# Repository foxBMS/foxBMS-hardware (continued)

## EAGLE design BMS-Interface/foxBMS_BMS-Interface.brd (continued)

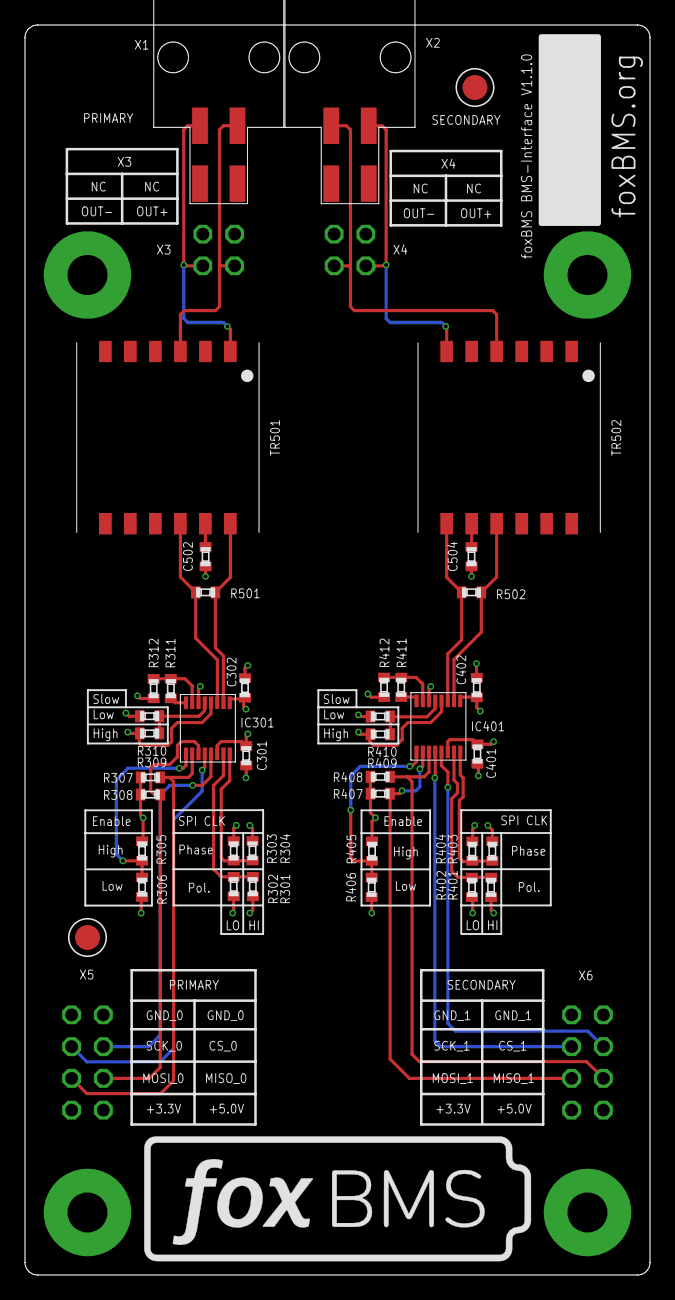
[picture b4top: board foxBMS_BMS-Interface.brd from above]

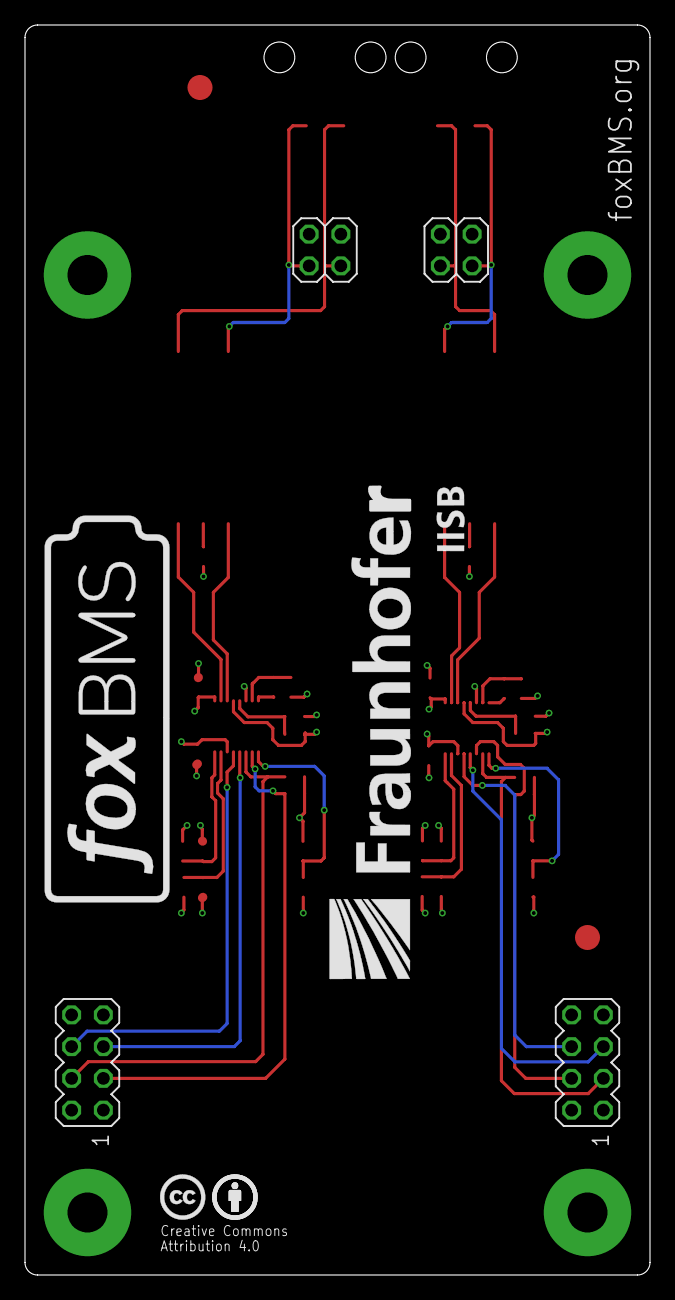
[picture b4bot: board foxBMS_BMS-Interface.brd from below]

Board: 4 copper layers, 50.0 x 100.0 mm, 44 parts (4 on the bottom side), 34 nets.

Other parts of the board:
TR501, TR502: HM2102NL
U$1, U$2: FIDUCIAL_1MM

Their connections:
unnamed 17: TR501.11; also elsewhere on the board
unnamed 23: TR502.8; also elsewhere on the board
PRIMARY_OUT+_P: TR501.3; also elsewhere on the board
PRIMARY_OUT-_N: TR501.1; also elsewhere on the board
PRIMARY_OUT_N: TR501.12; also elsewhere on the board
PRIMARY_OUT_P: TR501.10; also elsewhere on the board
SECONDARY_OUT+_P: TR502.6; also elsewhere on the board
SECONDARY_OUT-_N: TR502.4; also elsewhere on the board
SECONDARY_OUT_N: TR502.9; also elsewhere on the board
SECONDARY_OUT_P: TR502.7; also elsewhere on the board

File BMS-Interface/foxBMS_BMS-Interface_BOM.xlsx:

Populate | Qty | Value | Device | Package | Parts | Description | Farnell | Digikey | Mouser
no | 2 |  | HEADER_POS4_43045-0406 | 43045-0406 | X1, X2 | Molex - Micro-Fit 3.0 Series connector, 3.00mm (0.118) pitch header, 4 position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 | 2063766
yes | 2 |  | SSW-104-01-G-D | 2x 04 | X5, X6 | PIN HEADER | 1668340
yes | 2 |  | SSW-102-01-G-D | 2x 02 | X3, X4 | PIN HEADER | 1668329
yes | 4 | 100n | C_0603 | 603 | C301, C302, C401, C402 | Capacitor | 1828890
yes | 8 | 0R | R_0603 | 603 | R302, R304, R305, R310, R402, R404, R405, R410 | Resistor | 2059527
yes | 2 | 1.21k | R_0603 | 603 | R312, R412 | Resistor | 2059331
yes | 2 | 120 | R_0603 | 603 | R501, R502 | Resistor | 2303067
yes | 2 | 27pF | C_0603 | 603 | C502, C504 | Capacitor | 1414627
yes | 4 | 2k | R_0603 | 603 | R307, R308, R407, R408 | Resistor | 2059343
yes | 2 | 806 | R_0603 | 603 | R311, R411 | Resistor | 2059324
yes | 2 | HM2102NL | HM2102NL | HM2102NL | T501, T502
yes | 2 | LTC6820 | LTC6820 | MSOP16 | IC301, IC401 |  |  | LTC6820HMS#PBF-ND
no | 8 | OPT: 0R | R_0603 | 603 | R301, R303, R306, R309, R401, R403, R406, R409 | Resistor | 2059527

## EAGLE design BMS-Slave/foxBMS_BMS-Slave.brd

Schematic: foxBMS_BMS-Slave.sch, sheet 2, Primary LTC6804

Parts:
IC201: LTC6804HG-1#PBF; IC_SMD_SSOP-48_(G48)_R_LINEAR_REV01

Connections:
+3.0V_VREF2_0: IC201.34 (VREF2); also elsewhere on the board
+5.0V_VREG_0: IC201.37 (VREG); also elsewhere on the board
FUSED_VBAT-: IC201.30 (V-1), IC201.31 (V-2); also elsewhere on the board
PRIMARY-C0: IC201.26 (C0); also elsewhere on the board
PRIMARY-C1: IC201.24 (C1); also elsewhere on the board
PRIMARY-C2: IC201.22 (C2); also elsewhere on the board
PRIMARY-C3: IC201.20 (C3); also elsewhere on the board
PRIMARY-C4: IC201.18 (C4); also elsewhere on the board
PRIMARY-C5: IC201.16 (C5); also elsewhere on the board
PRIMARY-C6: IC201.14 (C6); also elsewhere on the board
PRIMARY-C7: IC201.12 (C7); also elsewhere on the board
PRIMARY-C8: IC201.10 (C8); also elsewhere on the board
PRIMARY-C9: IC201.8 (C9); also elsewhere on the board
PRIMARY-C10: IC201.6 (C10); also elsewhere on the board
PRIMARY-C11: IC201.4 (C11); also elsewhere on the board
PRIMARY-C12: IC201.2 (C12); also elsewhere on the board
PRIMARY-DRIVE: IC201.38 (DRIVE); also elsewhere on the board
PRIMARY-GPIO0: IC201.27 (GPIO1); also elsewhere on the board
PRIMARY-GPIO1: IC201.28 (GPIO2); also elsewhere on the board
PRIMARY-GPIO2: IC201.29 (GPIO3); also elsewhere on the board
PRIMARY-GPIO3: IC201.32 (GPIO4); also elsewhere on the board
PRIMARY-GPIO4: IC201.33 (GPIO5); also elsewhere on the board
PRIMARY-IBIAS: IC201.45 (IBIAS); also elsewhere on the board
PRIMARY-ICMP: IC201.46 (ICMP); also elsewhere on the board
PRIMARY-IN_N: IC201.41 (CSB/IMA); also elsewhere on the board
PRIMARY-IN_P: IC201.42 (SCK/IPA); also elsewhere on the board
PRIMARY-ISOMD: IC201.40 (ISOMD); also elsewhere on the board
PRIMARY-OUT_N: IC201.47 (IMB); also elsewhere on the board
PRIMARY-OUT_P: IC201.48 (IPB); also elsewhere on the board
PRIMARY-SWTEN: IC201.36 (SWTEN); also elsewhere on the board
PRIMARY-V+: IC201.1 (V+); also elsewhere on the board
PRIMARY-VREF1: IC201.35 (VREF1); also elsewhere on the board
PRIMARY-WDT: IC201.39 (WDT); also elsewhere on the board
S0: IC201.25 (S1); also elsewhere on the board
S1: IC201.23 (S2); also elsewhere on the board
S2: IC201.21 (S3); also elsewhere on the board
S3: IC201.19 (S4); also elsewhere on the board
S4: IC201.17 (S5); also elsewhere on the board
S5: IC201.15 (S6); also elsewhere on the board
S6: IC201.13 (S7); also elsewhere on the board
S7: IC201.11 (S8); also elsewhere on the board
S8: IC201.9 (S9); also elsewhere on the board
S9: IC201.7 (S10); also elsewhere on the board
S10: IC201.5 (S11); also elsewhere on the board
S11: IC201.3 (S12); also elsewhere on the board

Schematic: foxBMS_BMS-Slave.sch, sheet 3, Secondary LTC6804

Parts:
IC301: LTC6804HG-1#PBF; IC_SMD_SSOP-48_(G48)_R_LINEAR_REV01

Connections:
+3.0V_VREF2_1: IC301.34 (VREF2); also elsewhere on the board
+5.0V_VREG_1: IC301.37 (VREG); also elsewhere on the board
FUSED_VBAT-: IC301.30 (V-1), IC301.31 (V-2); also elsewhere on the board
SECONDARY-C0: IC301.26 (C0); also elsewhere on the board
SECONDARY-C1: IC301.24 (C1); also elsewhere on the board
SECONDARY-C2: IC301.22 (C2); also elsewhere on the board
SECONDARY-C3: IC301.20 (C3); also elsewhere on the board
SECONDARY-C4: IC301.18 (C4); also elsewhere on the board
SECONDARY-C5: IC301.16 (C5); also elsewhere on the board
SECONDARY-C6: IC301.14 (C6); also elsewhere on the board
SECONDARY-C7: IC301.12 (C7); also elsewhere on the board
SECONDARY-C8: IC301.10 (C8); also elsewhere on the board
SECONDARY-C9: IC301.8 (C9); also elsewhere on the board
SECONDARY-C10: IC301.6 (C10); also elsewhere on the board
SECONDARY-C11: IC301.4 (C11); also elsewhere on the board
SECONDARY-C12: IC301.2 (C12); also elsewhere on the board
SECONDARY-DRIVE: IC301.38 (DRIVE); also elsewhere on the board
SECONDARY-GPIO0: IC301.27 (GPIO1); also elsewhere on the board
SECONDARY-GPIO1: IC301.28 (GPIO2); also elsewhere on the board
SECONDARY-GPIO2: IC301.29 (GPIO3); also elsewhere on the board
SECONDARY-GPIO3: IC301.32 (GPIO4); also elsewhere on the board
SECONDARY-GPIO4: IC301.33 (GPIO5); also elsewhere on the board
SECONDARY-IBIAS: IC301.45 (IBIAS); also elsewhere on the board
SECONDARY-ICMP: IC301.46 (ICMP); also elsewhere on the board
SECONDARY-IN_N: IC301.41 (CSB/IMA); also elsewhere on the board
SECONDARY-IN_P: IC301.42 (SCK/IPA); also elsewhere on the board
SECONDARY-ISOMD: IC301.40 (ISOMD); also elsewhere on the board
SECONDARY-OUT_N: IC301.47 (IMB); also elsewhere on the board
SECONDARY-OUT_P: IC301.48 (IPB); also elsewhere on the board
SECONDARY-SWTEN: IC301.36 (SWTEN); also elsewhere on the board
SECONDARY-V+: IC301.1 (V+); also elsewhere on the board
SECONDARY-VREF1: IC301.35 (VREF1); also elsewhere on the board
SECONDARY-WDT: IC301.39 (WDT); also elsewhere on the board

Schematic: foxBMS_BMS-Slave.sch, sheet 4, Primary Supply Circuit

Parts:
C401, C403, C405: 1uF, 20%, 16V; 0603
C402, C404, C406: 100nF, 10%, 100V; 0805
LSP401, LSP402, LSP403: PAD_2.0X1.5MM; PAD2.0X1.5MM
R401, R402: 100R, 1%, 1/10W; 0603
T401: PBHV8115Z; D_SMD_SOT223_(SC-73)_R_NXP_REV01
Z401: 60V,500mW; D_SMD_SOD-123_R_ON_REV01

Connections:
+3.0V_VREF2_0: C401.2, LSP403.P$1; also elsewhere on the board
+5.0V_VREG_0: C405.2, LSP401.P$1, T401.3 (E); also elsewhere on the board
FUSED_VBAT+: R401.2, R402.1; also elsewhere on the board
FUSED_VBAT-: C401.1, C402.2, C403.1, C404.2, C405.1, C406.1, Z401.A; also elsewhere on the board
unnamed: C406.2, R401.1, T401.2 (C), T401.4 (C)
PRIMARY-DRIVE: T401.1 (B); also elsewhere on the board
PRIMARY-V+: C402.1, C404.1, R402.2, Z401.K (C); also elsewhere on the board
PRIMARY-VREF1: C403.2, LSP402.P$1; also elsewhere on the board

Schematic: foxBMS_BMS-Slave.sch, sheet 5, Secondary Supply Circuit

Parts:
C501, C503, C505: 1uF, 20%, 16V; 0603
C502, C504, C506: 100nF, 10%, 100V; 0805
LSP501, LSP502, LSP503: PAD_2.0X1.5MM; PAD2.0X1.5MM
R501, R502: 100R, 1%, 1/10W; 0603
T501: PBHV8115Z; D_SMD_SOT223_(SC-73)_R_NXP_REV01
Z501: 60V,500mW; D_SMD_SOD-123_R_ON_REV01

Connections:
+3.0V_VREF2_1: C501.2, LSP503.P$1; also elsewhere on the board
+5.0V_VREG_1: C505.2, LSP501.P$1, T501.3 (E); also elsewhere on the board
FUSED_VBAT+: R501.2, R502.1; also elsewhere on the board
FUSED_VBAT-: C501.1, C502.2, C503.1, C504.2, C505.1, C506.1, Z501.A; also elsewhere on the board
unnamed: C506.2, R501.1, T501.2 (C), T501.4 (C)
SECONDARY-DRIVE: T501.1 (B); also elsewhere on the board
SECONDARY-V+: C502.1, C504.1, R502.2, Z501.K (C); also elsewhere on the board
SECONDARY-VREF1: C503.2, LSP502.P$1; also elsewhere on the board

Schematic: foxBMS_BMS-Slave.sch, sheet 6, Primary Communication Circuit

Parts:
C601, C602: 100pF, 15%, 25V; 0603
C603, C604: 1uF, 20%, 25V; 0603
LSP601, LSP602, LSP603, LSP604: PAD_2.0X1.5MM; PAD2.0X1.5MM
R601, R607: 0R; 0603
R602: 806, 1%, 1/10W; 0603
R603: 1.21k, 1%, 1/10W; 0603
R604, R605: 120R, 1%, 1/10W; 0603
R606: OPT: 0R; 0603
R608: 1M, 10%, 1/10W; 0603
TR601: HX1188NL; TR_SMD_SOIC-16_(12,70MMX9,53MMX5,97MM)_R_PULSE_REV01

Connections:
+5.0V_VREG_0: R601.2, R606.2, R608.2; also elsewhere on the board
FUSED_VBAT-: C601.1, C602.1, R603.2, R607.1; also elsewhere on the board
GND_1: C603.1, C604.1; also elsewhere on the board
unnamed: C601.2, TR601.2 (CT)
unnamed: C602.2, TR601.7 (CT)
unnamed: C604.2, TR601.15 (CMT)
unnamed: C603.2, TR601.10 (CMT)
PRIMARY-IBIAS: R602.1; also elsewhere on the board
PRIMARY-ICMP: R602.2, R603.1; also elsewhere on the board
PRIMARY-IN+_P: LSP601.P$1, TR601.16 (X+); also elsewhere on the board
PRIMARY-IN-_N: LSP602.P$1, TR601.14 (X-); also elsewhere on the board
PRIMARY-IN_N: R604.2, TR601.3 (D-); also elsewhere on the board
PRIMARY-IN_P: R604.1, TR601.1 (D+); also elsewhere on the board
PRIMARY-ISOMD: R601.1; also elsewhere on the board
PRIMARY-OUT+_P: LSP603.P$1, TR601.11 (X+); also elsewhere on the board
PRIMARY-OUT-_N: LSP604.P$1, TR601.9 (X-); also elsewhere on the board
PRIMARY-OUT_N: R605.2, TR601.8 (D-); also elsewhere on the board
PRIMARY-OUT_P: R605.1, TR601.6 (D+); also elsewhere on the board
PRIMARY-SWTEN: R606.1, R607.2; also elsewhere on the board
PRIMARY-WDT: R608.1; also elsewhere on the board

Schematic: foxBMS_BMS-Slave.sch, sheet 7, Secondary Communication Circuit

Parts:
C701, C702: 100pF, 15%, 25V; 0603
C703, C704: 1uF, 20%, 25V; 0603
LSP701, LSP702, LSP703, LSP704: PAD_2.0X1.5MM; PAD2.0X1.5MM
R701, R707: 0R; 0603
R702: 806, 1%, 1/10W; 0603
R703: 1.21k, 1%, 1/10W; 0603
R704, R705: 120R, 1%, 1/10W; 0603
R706: OPT: 0R; 0603
R708: 1M, 10%, 1/10W; 0603
TR701: HX1188NL; TR_SMD_SOIC-16_(12,70MMX9,53MMX5,97MM)_R_PULSE_REV01

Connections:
+5.0V_VREG_1: R701.2, R706.2, R708.2; also elsewhere on the board
FUSED_VBAT-: C701.1, C702.1, R703.2, R707.1; also elsewhere on the board
GND_1: C703.1, C704.1; also elsewhere on the board
unnamed: C701.2, TR701.2 (CT)
unnamed: C702.2, TR701.7 (CT)
unnamed: C704.2, TR701.15 (CMT)
unnamed: C703.2, TR701.10 (CMT)
SECONDARY-IBIAS: R702.1; also elsewhere on the board
SECONDARY-ICMP: R702.2, R703.1; also elsewhere on the board
SECONDARY-IN+_P: LSP701.P$1, TR701.16 (X+); also elsewhere on the board
SECONDARY-IN-_N: LSP702.P$1, TR701.14 (X-); also elsewhere on the board
SECONDARY-IN_N: R704.2, TR701.3 (D-); also elsewhere on the board
SECONDARY-IN_P: R704.1, TR701.1 (D+); also elsewhere on the board
SECONDARY-ISOMD: R701.1; also elsewhere on the board
SECONDARY-OUT+_P: LSP703.P$1, TR701.11 (X+); also elsewhere on the board
SECONDARY-OUT-_N: LSP704.P$1, TR701.9 (X-); also elsewhere on the board
SECONDARY-OUT_N: R705.2, TR701.8 (D-); also elsewhere on the board
SECONDARY-OUT_P: R705.1, TR701.6 (D+); also elsewhere on the board
SECONDARY-SWTEN: R706.1, R707.2; also elsewhere on the board
SECONDARY-WDT: R708.1; also elsewhere on the board

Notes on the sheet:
standard = off

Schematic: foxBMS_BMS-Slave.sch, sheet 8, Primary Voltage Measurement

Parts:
C801, C802, C803, C804, C805, C806, C807, C815, C816, C817, C818, C819, C820: 10nF, 100V, 10%; 0603
C808, C809, C810, C811, C812, C813, C814, C821, C822, C823, C824, C825, C826: OPT: 100nF, 25V; 0805
R801, R802, R803, R804, R805, R806, R807, R808, R809, R810, R811, R812, R813: 100R, 1%, 1/10W; 0603
Z801, Z802, Z803, Z804, Z805, Z806, Z807, Z808, Z809, Z810, Z811, Z812, Z813: 6.8V, 500mW; D_SMD_SOD-123_R_ON_REV01

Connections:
FUSED_CELL_0+: R806.1; also elsewhere on the board
FUSED_CELL_0-: R807.1; also elsewhere on the board
FUSED_CELL_1+: R805.1; also elsewhere on the board
FUSED_CELL_2+: R804.1; also elsewhere on the board
FUSED_CELL_3+: R803.1; also elsewhere on the board
FUSED_CELL_4+: R802.1; also elsewhere on the board
FUSED_CELL_5+: R801.1; also elsewhere on the board
FUSED_CELL_6+: R813.1; also elsewhere on the board
FUSED_CELL_7+: R812.1; also elsewhere on the board
FUSED_CELL_8+: R811.1; also elsewhere on the board
FUSED_CELL_9+: R810.1; also elsewhere on the board
FUSED_CELL_10+: R809.1; also elsewhere on the board
FUSED_CELL_11+: R808.1; also elsewhere on the board
FUSED_VBAT-: C801.2, C802.2, C803.2, C804.2, C805.2, C806.2, C807.2, C814.1, C815.2, C816.2, C817.2, C818.2, C819.2, C820.2, Z807.A; also elsewhere on the board
PRIMARY-C0: C807.1, C813.1, C814.2, R807.2, Z806.A, Z807.K (C); also elsewhere on the board
PRIMARY-C1: C806.1, C812.1, C813.2, R806.2, Z805.A, Z806.K (C); also elsewhere on the board
PRIMARY-C2: C805.1, C811.1, C812.2, R805.2, Z804.A, Z805.K (C); also elsewhere on the board
PRIMARY-C3: C804.1, C810.1, C811.2, R804.2, Z803.A, Z804.K (C); also elsewhere on the board
PRIMARY-C4: C803.1, C809.1, C810.2, R803.2, Z802.A, Z803.K (C); also elsewhere on the board
PRIMARY-C5: C802.1, C808.1, C809.2, R802.2, Z801.A, Z802.K (C); also elsewhere on the board
PRIMARY-C6: C801.1, C808.2, C826.1, R801.2, Z801.K (C), Z813.A; also elsewhere on the board
PRIMARY-C7: C820.1, C825.1, C826.2, R813.2, Z812.A, Z813.K (C); also elsewhere on the board
PRIMARY-C8: C819.1, C824.1, C825.2, R812.2, Z811.A, Z812.K (C); also elsewhere on the board
PRIMARY-C9: C818.1, C823.1, C824.2, R811.2, Z810.A, Z811.K (C); also elsewhere on the board
PRIMARY-C10: C817.1, C822.1, C823.2, R810.2, Z809.A, Z810.K (C); also elsewhere on the board
PRIMARY-C11: C816.1, C821.1, C822.2, R809.2, Z808.A, Z809.K (C); also elsewhere on the board
PRIMARY-C12: C815.1, C821.2, R808.2, Z808.K (C); also elsewhere on the board

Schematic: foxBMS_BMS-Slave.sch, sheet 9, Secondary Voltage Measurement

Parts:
C901, C902, C903, C904, C905, C906, C907, C915, C916, C917, C918, C919, C920: 10nF, 100V, 10%; 0603
C908, C909, C910, C911, C912, C913, C914, C921, C922, C923, C924, C925, C926: OPT: 100nF, 25V; 0805
R901, R902, R903, R904, R905, R906, R907, R908, R909, R910, R911, R912, R913: 100R, 1%, 1/10W; 0603
Z901, Z902, Z903, Z904, Z905, Z906, Z907, Z908, Z909, Z910, Z911, Z912, Z913: 6.8V, 500mW; D_SMD_SOD-123_R_ON_REV01

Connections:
FUSED_CELL_0+: R906.1; also elsewhere on the board
FUSED_CELL_0-: R907.1; also elsewhere on the board
FUSED_CELL_1+: R905.1; also elsewhere on the board
FUSED_CELL_2+: R904.1; also elsewhere on the board
FUSED_CELL_3+: R903.1; also elsewhere on the board
FUSED_CELL_4+: R902.1; also elsewhere on the board
FUSED_CELL_5+: R901.1; also elsewhere on the board
FUSED_CELL_6+: R913.1; also elsewhere on the board
FUSED_CELL_7+: R912.1; also elsewhere on the board
FUSED_CELL_8+: R911.1; also elsewhere on the board
FUSED_CELL_9+: R910.1; also elsewhere on the board
FUSED_CELL_10+: R909.1; also elsewhere on the board
FUSED_CELL_11+: R908.1; also elsewhere on the board
FUSED_VBAT-: C901.2, C902.2, C903.2, C904.2, C905.2, C906.2, C907.2, C914.1, C915.2, C916.2, C917.2, C918.2, C919.2, C920.2, Z907.A; also elsewhere on the board
SECONDARY-C0: C907.1, C913.1, C914.2, R907.2, Z906.A, Z907.K (C); also elsewhere on the board
SECONDARY-C1: C906.1, C912.1, C913.2, R906.2, Z905.A, Z906.K (C); also elsewhere on the board
SECONDARY-C2: C905.1, C911.1, C912.2, R905.2, Z904.A, Z905.K (C); also elsewhere on the board
SECONDARY-C3: C904.1, C910.1, C911.2, R904.2, Z903.A, Z904.K (C); also elsewhere on the board
SECONDARY-C4: C903.1, C909.1, C910.2, R903.2, Z902.A, Z903.K (C); also elsewhere on the board
SECONDARY-C5: C902.1, C908.1, C909.2, R902.2, Z901.A, Z902.K (C); also elsewhere on the board
SECONDARY-C6: C901.1, C908.2, C926.1, R901.2, Z901.K (C), Z913.A; also elsewhere on the board
SECONDARY-C7: C920.1, C925.1, C926.2, R913.2, Z912.A, Z913.K (C); also elsewhere on the board
SECONDARY-C8: C919.1, C924.1, C925.2, R912.2, Z911.A, Z912.K (C); also elsewhere on the board
SECONDARY-C9: C918.1, C923.1, C924.2, R911.2, Z910.A, Z911.K (C); also elsewhere on the board
SECONDARY-C10: C917.1, C922.1, C923.2, R910.2, Z909.A, Z910.K (C); also elsewhere on the board
SECONDARY-C11: C916.1, C921.1, C922.2, R909.2, Z908.A, Z909.K (C); also elsewhere on the board
SECONDARY-C12: C915.1, C921.2, R908.2, Z908.K (C); also elsewhere on the board

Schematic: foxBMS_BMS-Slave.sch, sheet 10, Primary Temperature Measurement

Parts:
C1001: 100nF, 20%, 16V; 0603
C1002, C1003, C1004: 1uF, 20%, 16V; 0603
C1005: 10nF, 20%, 16V; 0603
M1001, M1002: LTC1380CGN; IC_SMD_SSOP-16_(GN16)_R_LINEAR_REV01
O1001: LTC6255CS6; IC_SMD_TSOT-23-6_(S6)_R_LINEAR_REV01
R1001, R1002, R1003, R1004, R1005, R1006, R1007, R1008, R1009, R1010, R1011, R1012, R1013, R1014, R1015, R1016: 20k, 1%, 1/10W; 0603
R1017, R1018: 4.7k, 10%, 1/10W; 0603
R1019, R1021, R1023: N/A; 0603
R1020, R1022, R1024: 0R; 0603
R1025: 100R, 1%, 1/10W; 0603
SJ1001: OPT; SJ

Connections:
+3.0V_VREF2_0: C1001.2, R1001.2, R1002.2, R1003.2, R1004.2, R1005.2, R1006.2, R1007.2, R1008.2, R1009.2, R1010.2, R1011.2, R1012.2, R1013.2, R1014.2, R1015.2, R1016.2; also elsewhere on the board
+5.0V_VREG_0: C1002.2, C1003.2, C1004.2, M1001.16 (VCC), M1002.13 (A0), M1002.16 (VCC), O1001.6 (V+), R1017.2, R1018.2; also elsewhere on the board
FUSED_VBAT-: C1001.1, C1002.1, C1003.1, C1004.1, C1005.1, M1001.10 (VEE), M1001.11 (GND), M1001.12 (A1), M1001.13 (A0), M1002.10 (VEE), M1002.11 (GND), M1002.12 (A1), O1001.2 (V-); also elsewhere on the board
unnamed: O1001.1 (VOUT), O1001.4 (-), R1025.1
unnamed: O1001.5 (!SHDN), SJ1001.1
PRIMARY-GPIO0: R1023.2, R1024.2; also elsewhere on the board
PRIMARY-GPIO0-OPT: R1023.1; also elsewhere on the board
PRIMARY-GPIO2: SJ1001.2; also elsewhere on the board
PRIMARY-GPIO3: R1021.2, R1022.2; also elsewhere on the board
PRIMARY-GPIO3-OPT: R1021.1; also elsewhere on the board
PRIMARY-GPIO4: R1019.2, R1020.2; also elsewhere on the board
PRIMARY-GPIO4-OPT: R1019.1; also elsewhere on the board
PRIMARY-MUX-DATA: C1005.2, R1024.1, R1025.2
PRIMARY-OPA_IN: M1001.9 (DO), M1002.9 (DO), O1001.3 (+); also elsewhere on the board
PRIMARY-SCL: M1001.15 (SCL), M1002.15 (SCL), R1017.1, R1020.1; also elsewhere on the board
PRIMARY-SDA: M1001.14 (SDA), M1002.14 (SDA), R1018.1, R1022.1; also elsewhere on the board
T-SENSOR_0: M1001.1 (S0), R1015.1; also elsewhere on the board
T-SENSOR_1: M1001.2 (S1), R1013.1; also elsewhere on the board
T-SENSOR_2: M1001.3 (S2), R1011.1; also elsewhere on the board
T-SENSOR_3: M1001.4 (S3), R1009.1; also elsewhere on the board
T-SENSOR_4: M1001.5 (S4), R1007.1; also elsewhere on the board
T-SENSOR_5: M1001.6 (S5), R1005.1; also elsewhere on the board
T-SENSOR_6: M1001.7 (S6), R1003.1; also elsewhere on the board
T-SENSOR_7: M1001.8 (S7), R1001.1; also elsewhere on the board
T-SENSOR_8: M1002.1 (S0), R1016.1; also elsewhere on the board
T-SENSOR_9: M1002.2 (S1), R1014.1; also elsewhere on the board
T-SENSOR_10: M1002.3 (S2), R1012.1; also elsewhere on the board
T-SENSOR_11: M1002.4 (S3), R1010.1; also elsewhere on the board
T-SENSOR_12: M1002.5 (S4), R1008.1; also elsewhere on the board
T-SENSOR_13: M1002.6 (S5), R1006.1; also elsewhere on the board
T-SENSOR_14: M1002.7 (S6), R1004.1; also elsewhere on the board
T-SENSOR_15: M1002.8 (S7), R1002.1; also elsewhere on the board

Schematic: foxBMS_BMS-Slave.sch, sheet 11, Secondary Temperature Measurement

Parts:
C1101: 100nF, 20%, 16V; 0603
C1102, C1103, C1104: 1uF, 20%, 16V; 0603
C1105: 10nF, 20%, 16V; 0603
M1101, M1102: LTC1380CGN; IC_SMD_SSOP-16_(GN16)_R_LINEAR_REV01
O1101: LTC6255CS6; IC_SMD_TSOT-23-6_(S6)_R_LINEAR_REV01
R1101, R1102, R1103, R1104, R1105, R1106, R1107, R1108, R1109, R1110, R1111, R1112, R1113, R1114, R1115, R1116: 20k, 1%, 1/10W; 0603
R1117, R1118: 4.7k, 10%, 1/10W; 0603
R1119, R1121, R1123: OPT: 0R; 0603
R1120, R1122, R1124: 0R; 0603
R1125: 100R, 1%, 1/10W; 0603
SJ1101: OPT; SJ

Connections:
+3.0V_VREF2_1: C1101.2, R1101.2, R1102.2, R1103.2, R1104.2, R1105.2, R1106.2, R1107.2, R1108.2, R1109.2, R1110.2, R1111.2, R1112.2, R1113.2, R1114.2, R1115.2, R1116.2; also elsewhere on the board
+5.0V_VREG_1: C1102.2, C1103.2, C1104.2, M1101.16 (VCC), M1102.13 (A0), M1102.16 (VCC), O1101.6 (V+), R1117.2, R1118.2; also elsewhere on the board
FUSED_VBAT-: C1101.1, C1102.1, C1103.1, C1104.1, C1105.1, M1101.10 (VEE), M1101.11 (GND), M1101.12 (A1), M1101.13 (A0), M1102.10 (VEE), M1102.11 (GND), M1102.12 (A1), O1101.2 (V-); also elsewhere on the board
unnamed: O1101.5 (!SHDN), SJ1101.1
unnamed: O1101.1 (VOUT), O1101.4 (-), R1125.1
SECONDARY-GPIO0: R1123.2, R1124.2; also elsewhere on the board
SECONDARY-GPIO0-OPT: R1123.1; also elsewhere on the board
SECONDARY-GPIO2: SJ1101.2; also elsewhere on the board
SECONDARY-GPIO3: R1121.2, R1122.2; also elsewhere on the board
SECONDARY-GPIO3-OPT: R1121.1; also elsewhere on the board
SECONDARY-GPIO4: R1119.2, R1120.2; also elsewhere on the board
SECONDARY-GPIO4-OPT: R1119.1; also elsewhere on the board
SECONDARY-MUX-DATA: C1105.2, R1124.1, R1125.2
SECONDARY-OPA_IN: M1101.9 (DO), M1102.9 (DO), O1101.3 (+); also elsewhere on the board
SECONDARY-SCL: M1101.15 (SCL), M1102.15 (SCL), R1117.1, R1120.1; also elsewhere on the board
SECONDARY-SDA: M1101.14 (SDA), M1102.14 (SDA), R1118.1, R1122.1; also elsewhere on the board
T-SENSOR_16: M1101.1 (S0), R1115.1; also elsewhere on the board
T-SENSOR_17: M1101.2 (S1), R1113.1; also elsewhere on the board
T-SENSOR_18: M1101.3 (S2), R1111.1; also elsewhere on the board
T-SENSOR_19: M1101.4 (S3), R1109.1; also elsewhere on the board
T-SENSOR_20: M1101.5 (S4), R1107.1; also elsewhere on the board
T-SENSOR_21: M1101.6 (S5), R1105.1; also elsewhere on the board
T-SENSOR_22: M1101.7 (S6), R1103.1; also elsewhere on the board
T-SENSOR_23: M1101.8 (S7), R1101.1; also elsewhere on the board
T-SENSOR_24: M1102.1 (S0), R1116.1; also elsewhere on the board
T-SENSOR_25: M1102.2 (S1), R1114.1; also elsewhere on the board
T-SENSOR_26: M1102.3 (S2), R1112.1; also elsewhere on the board
T-SENSOR_27: M1102.4 (S3), R1110.1; also elsewhere on the board
T-SENSOR_28: M1102.5 (S4), R1108.1; also elsewhere on the board
T-SENSOR_29: M1102.6 (S5), R1106.1; also elsewhere on the board
T-SENSOR_30: M1102.7 (S6), R1104.1; also elsewhere on the board
T-SENSOR_31: M1102.8 (S7), R1102.1; also elsewhere on the board

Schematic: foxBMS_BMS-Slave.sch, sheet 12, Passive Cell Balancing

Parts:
R1201, R1202, R1203, R1204, R1205, R1206, R1207, R1208, R1209, R1210, R1211, R1212, R1219, R1220, R1221, R1222, R1223, R1224, R1225, R1226, R1227, R1228, R1229, R1230: 75R, 10%, 0.4W; 2010
R1213, R1214, R1215, R1216, R1217, R1218, R1231, R1232, R1233, R1234, R1235, R1236: 3.3k, 10%, 1/10W; 0603
T1201, T1202, T1203, T1204, T1205, T1206, T1207, T1208, T1209, T1210, T1211, T1212: NX2301P; D_SMD_SOT23_(TO-236AB)_R_NXP_REV01

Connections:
CELL0_FEEDBACK+: R1206.2, R1212.2, T1206.3 (D); also elsewhere on the board
CELL1_FEEDBACK+: R1205.2, R1211.2, T1205.3 (D); also elsewhere on the board
CELL2_FEEDBACK+: R1204.2, R1210.2, T1204.3 (D); also elsewhere on the board
CELL3_FEEDBACK+: R1203.2, R1209.2, T1203.3 (D); also elsewhere on the board
CELL4_FEEDBACK+: R1202.2, R1208.2, T1202.3 (D); also elsewhere on the board
CELL5_FEEDBACK+: R1201.2, R1207.2, T1201.3 (D); also elsewhere on the board
CELL6_FEEDBACK+: R1224.2, R1230.2, T1212.3 (D); also elsewhere on the board
CELL7_FEEDBACK+: R1223.2, R1229.2, T1211.3 (D); also elsewhere on the board
CELL8_FEEDBACK+: R1222.2, R1228.2, T1210.3 (D); also elsewhere on the board
CELL9_FEEDBACK+: R1221.2, R1227.2, T1209.3 (D); also elsewhere on the board
CELL10_FEEDBACK+: R1220.2, R1226.2, T1208.3 (D); also elsewhere on the board
CELL11_FEEDBACK+: R1219.2, R1225.2, T1207.3 (D); also elsewhere on the board
FUSED_CELL_0+: R1205.1, R1211.1, T1206.2 (S); also elsewhere on the board
FUSED_CELL_1+: R1204.1, R1210.1, T1205.2 (S); also elsewhere on the board
FUSED_CELL_2+: R1203.1, R1209.1, T1204.2 (S); also elsewhere on the board
FUSED_CELL_3+: R1202.1, R1208.1, T1203.2 (S); also elsewhere on the board
FUSED_CELL_4+: R1201.1, R1207.1, T1202.2 (S); also elsewhere on the board
FUSED_CELL_5+: R1224.1, R1230.1, T1201.2 (S); also elsewhere on the board
FUSED_CELL_6+: R1223.1, R1229.1, T1212.2 (S); also elsewhere on the board
FUSED_CELL_7+: R1222.1, R1228.1, T1211.2 (S); also elsewhere on the board
FUSED_CELL_8+: R1221.1, R1227.1, T1210.2 (S); also elsewhere on the board
FUSED_CELL_9+: R1220.1, R1226.1, T1209.2 (S); also elsewhere on the board
FUSED_CELL_10+: R1219.1, R1225.1, T1208.2 (S); also elsewhere on the board
FUSED_CELL_11+: T1207.2 (S); also elsewhere on the board
FUSED_VBAT-: R1206.1, R1212.1; also elsewhere on the board
unnamed: R1218.1, T1206.1 (G)
unnamed: R1216.1, T1205.1 (G)
unnamed: R1217.1, T1204.1 (G)
unnamed: R1215.1, T1203.1 (G)
unnamed: R1214.1, T1202.1 (G)
unnamed: R1213.1, T1201.1 (G)
unnamed: R1232.1, T1212.1 (G)
unnamed: R1236.1, T1211.1 (G)
unnamed: R1235.1, T1210.1 (G)
unnamed: R1234.1, T1209.1 (G)
unnamed: R1233.1, T1208.1 (G)
unnamed: R1231.1, T1207.1 (G)
S0: R1218.2; also elsewhere on the board
S1: R1216.2; also elsewhere on the board
S2: R1217.2; also elsewhere on the board
S3: R1215.2; also elsewhere on the board
S4: R1214.2; also elsewhere on the board
S5: R1213.2; also elsewhere on the board
S6: R1232.2; also elsewhere on the board
S7: R1236.2; also elsewhere on the board
S8: R1235.2; also elsewhere on the board
S9: R1234.2; also elsewhere on the board
S10: R1233.2; also elsewhere on the board
S11: R1231.2; also elsewhere on the board

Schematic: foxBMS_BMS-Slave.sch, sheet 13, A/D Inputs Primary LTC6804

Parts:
C1301, C1302: 1uF, 20%, 16V; 0603
M1301, M1302: LTC1380CGN; IC_SMD_SSOP-16_(GN16)_R_LINEAR_REV01
R1301, R1302, R1303, R1304, R1305, R1306, R1307, R1308, R1309, R1310, R1311, R1312, R1313, R1314, R1315, R1316: 10k, 10%, 1/10W; 0603

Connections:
+5.0V_VREG_0: C1301.2, C1302.2, M1301.12 (A1), M1301.16 (VCC), M1302.12 (A1), M1302.13 (A0), M1302.16 (VCC); also elsewhere on the board
FUSED_VBAT-: C1301.1, C1302.1, M1301.10 (VEE), M1301.11 (GND), M1301.13 (A0), M1302.10 (VEE), M1302.11 (GND), R1301.2, R1302.2, R1303.2, R1304.2, R1305.2, R1306.2, R1307.2, R1308.2, R1309.2, R1310.2, R1311.2, R1312.2, R1313.2, R1314.2, R1315.2, R1316.2; also elsewhere on the board
PRIMARY-OPA_IN: M1301.9 (DO), M1302.9 (DO); also elsewhere on the board
PRIMARY-SCL: M1301.15 (SCL), M1302.15 (SCL); also elsewhere on the board
PRIMARY-SDA: M1301.14 (SDA), M1302.14 (SDA); also elsewhere on the board
PRIMARY_D/A_INPUT_0: M1301.1 (S0), R1301.1; also elsewhere on the board
PRIMARY_D/A_INPUT_1: M1301.2 (S1), R1302.1; also elsewhere on the board
PRIMARY_D/A_INPUT_2: M1301.3 (S2), R1303.1; also elsewhere on the board
PRIMARY_D/A_INPUT_3: M1301.4 (S3), R1304.1; also elsewhere on the board
PRIMARY_D/A_INPUT_4: M1301.5 (S4), R1305.1; also elsewhere on the board
PRIMARY_D/A_INPUT_5: M1301.6 (S5), R1306.1; also elsewhere on the board
PRIMARY_D/A_INPUT_6: M1301.7 (S6), R1307.1; also elsewhere on the board
PRIMARY_D/A_INPUT_7: M1301.8 (S7), R1308.1; also elsewhere on the board
PRIMARY_D/A_INPUT_8: M1302.1 (S0), R1309.1; also elsewhere on the board
PRIMARY_D/A_INPUT_9: M1302.2 (S1), R1310.1; also elsewhere on the board
PRIMARY_D/A_INPUT_10: M1302.3 (S2), R1311.1; also elsewhere on the board
PRIMARY_D/A_INPUT_11: M1302.4 (S3), R1312.1; also elsewhere on the board
PRIMARY_D/A_INPUT_12: M1302.5 (S4), R1313.1; also elsewhere on the board
PRIMARY_D/A_INPUT_13: M1302.6 (S5), R1314.1; also elsewhere on the board
PRIMARY_D/A_INPUT_14: M1302.7 (S6), R1315.1; also elsewhere on the board
PRIMARY_D/A_INPUT_15: M1302.8 (S7), R1316.1; also elsewhere on the board

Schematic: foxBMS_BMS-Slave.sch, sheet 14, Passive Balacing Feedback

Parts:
C1401, C1402: 1uF, 20%, 16V; 0603
IC1401, IC1402, IC1403, IC1404, IC1405, IC1406, IC1407, IC1408, IC1409, IC1410, IC1411, IC1412: CPC1008N; K_SMD_SOP-4_R_IXYS_REV01
M1401, M1402: LTC1380CGN; IC_SMD_SSOP-16_(GN16)_R_LINEAR_REV01
R1401, R1402, R1403, R1404, R1405, R1406, R1408, R1409, R1410, R1411, R1412, R1413: 130, 10%, 1/10W; 0603
R1407: 1k, 10%, 1/10W; 0603
R1414, R1415, R1416, R1417, R1418, R1419, R1420, R1421, R1422, R1423, R1424, R1425, R1426, R1427, R1428, R1429: 10k, 10%, 1/10W; 0603

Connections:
+5.0V_VREG_1: C1401.2, C1402.2, M1401.12 (A1), M1401.16 (VCC), M1402.12 (A1), M1402.13 (A0), M1402.16 (VCC), R1407.1; also elsewhere on the board
CELL0_FEEDBACK: IC1406.3, M1401.1 (S0), R1414.1
CELL0_FEEDBACK+: R1406.2; also elsewhere on the board
CELL1_FEEDBACK: IC1405.3, M1401.2 (S1), R1415.1
CELL1_FEEDBACK+: R1405.2; also elsewhere on the board
CELL2_FEEDBACK: IC1404.3, M1401.3 (S2), R1416.1
CELL2_FEEDBACK+: R1404.2; also elsewhere on the board
CELL3_FEEDBACK: IC1403.3, M1401.4 (S3), R1417.1
CELL3_FEEDBACK+: R1403.2; also elsewhere on the board
CELL4_FEEDBACK: IC1402.3, M1401.5 (S4), R1418.1
CELL4_FEEDBACK+: R1402.2; also elsewhere on the board
CELL5_FEEDBACK: IC1401.3, M1401.6 (S5), R1419.1
CELL5_FEEDBACK+: R1401.2; also elsewhere on the board
CELL6_FEEDBACK: IC1412.3, M1401.7 (S6), R1420.1
CELL6_FEEDBACK+: R1413.2; also elsewhere on the board
CELL7_FEEDBACK: IC1411.3, M1401.8 (S7), R1421.1
CELL7_FEEDBACK+: R1412.2; also elsewhere on the board
CELL8_FEEDBACK: IC1410.3, M1402.1 (S0), R1422.1
CELL8_FEEDBACK+: R1411.2; also elsewhere on the board
CELL9_FEEDBACK: IC1409.3, M1402.2 (S1), R1423.1
CELL9_FEEDBACK+: R1410.2; also elsewhere on the board
CELL10_FEEDBACK: IC1408.3, M1402.3 (S2), R1424.1
CELL10_FEEDBACK+: R1409.2; also elsewhere on the board
CELL11_FEEDBACK: IC1407.3, M1402.4 (S3), R1425.1
CELL11_FEEDBACK+: R1408.2; also elsewhere on the board
FUSED_CELL_0+: IC1405.2 (CON-); also elsewhere on the board
FUSED_CELL_1+: IC1404.2 (CON-); also elsewhere on the board
FUSED_CELL_2+: IC1403.2 (CON-); also elsewhere on the board
FUSED_CELL_3+: IC1402.2 (CON-); also elsewhere on the board
FUSED_CELL_4+: IC1401.2 (CON-); also elsewhere on the board
FUSED_CELL_5+: IC1412.2 (CON-); also elsewhere on the board
FUSED_CELL_6+: IC1411.2 (CON-); also elsewhere on the board
FUSED_CELL_7+: IC1410.2 (CON-); also elsewhere on the board
FUSED_CELL_8+: IC1409.2 (CON-); also elsewhere on the board
FUSED_CELL_9+: IC1408.2 (CON-); also elsewhere on the board
FUSED_CELL_10+: IC1407.2 (CON-); also elsewhere on the board
FUSED_VBAT-: C1401.1, C1402.1, IC1406.2 (CON-), M1401.10 (VEE), M1401.11 (GND), M1401.13 (A0), M1402.10 (VEE), M1402.11 (GND), R1414.2, R1415.2, R1416.2, R1417.2, R1418.2, R1419.2, R1420.2, R1421.2, R1422.2, R1423.2, R1424.2, R1425.2, R1426.2, R1427.2, R1428.2, R1429.2; also elsewhere on the board
unnamed: IC1401.4, IC1402.4, IC1403.4, IC1404.4, IC1405.4, IC1406.4, IC1407.4, IC1408.4, IC1409.4, IC1410.4, IC1411.4, IC1412.4, R1407.2
unnamed: IC1402.1 (CON+), R1402.1
unnamed: IC1403.1 (CON+), R1403.1
unnamed: IC1404.1 (CON+), R1404.1
unnamed: IC1408.1 (CON+), R1409.1
unnamed: IC1409.1 (CON+), R1410.1
unnamed: IC1405.1 (CON+), R1405.1
unnamed: IC1407.1 (CON+), R1408.1
unnamed: IC1410.1 (CON+), R1411.1
unnamed: IC1411.1 (CON+), R1412.1
unnamed: IC1406.1 (CON+), R1406.1
unnamed: IC1412.1 (CON+), R1413.1
unnamed: IC1401.1 (CON+), R1401.1
SECONDARY-OPA_IN: M1401.9 (DO), M1402.9 (DO); also elsewhere on the board
SECONDARY-SCL: M1401.15 (SCL), M1402.15 (SCL); also elsewhere on the board
SECONDARY-SDA: M1401.14 (SDA), M1402.14 (SDA); also elsewhere on the board
SECONDARY_D/A_INPUT_0: M1402.5 (S4), R1426.1; also elsewhere on the board
SECONDARY_D/A_INPUT_1: M1402.6 (S5), R1427.1; also elsewhere on the board
SECONDARY_D/A_INPUT_2: M1402.7 (S6), R1428.1; also elsewhere on the board
SECONDARY_D/A_INPUT_3: M1402.8 (S7), R1429.1; also elsewhere on the board

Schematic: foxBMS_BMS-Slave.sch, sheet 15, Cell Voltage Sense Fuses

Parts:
F1501, F1515: 0.5A, 63V, 0.25R; 1206
F1502, F1503, F1504, F1505, F1506, F1507, F1508, F1509, F1510, F1511, F1512, F1513, F1514: FUSE: 0.250A, 32V, 0.57R; 0603
LSP1501, LSP1502, LSP1503, LSP1504, LSP1505, LSP1506, LSP1507, LSP1508, LSP1509, LSP1510, LSP1511, LSP1512, LSP1513, LSP1514, LSP1515: PAD_2.0X1.5MM; PAD2.0X1.5MM
SJ1501, SJ1502: SJ

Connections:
CELL_0+: F1503.1; also elsewhere on the board
CELL_0-: F1502.1, SJ1501.1; also elsewhere on the board
CELL_1+: F1504.1; also elsewhere on the board
CELL_2+: F1505.1; also elsewhere on the board
CELL_3+: F1506.1; also elsewhere on the board
CELL_4+: F1507.1; also elsewhere on the board
CELL_5+: F1508.1; also elsewhere on the board
CELL_6+: F1509.1; also elsewhere on the board
CELL_7+: F1510.1; also elsewhere on the board
CELL_8+: F1511.1; also elsewhere on the board
CELL_9+: F1512.1; also elsewhere on the board
CELL_10+: F1513.1; also elsewhere on the board
CELL_11+: F1514.1, SJ1502.2; also elsewhere on the board
FUSED_CELL_0+: F1503.2, LSP1503.P$1; also elsewhere on the board
FUSED_CELL_0-: F1502.2, LSP1502.P$1; also elsewhere on the board
FUSED_CELL_1+: F1504.2, LSP1504.P$1; also elsewhere on the board
FUSED_CELL_2+: F1505.2, LSP1505.P$1; also elsewhere on the board
FUSED_CELL_3+: F1506.2, LSP1506.P$1; also elsewhere on the board
FUSED_CELL_4+: F1507.2, LSP1507.P$1; also elsewhere on the board
FUSED_CELL_5+: F1508.2, LSP1508.P$1; also elsewhere on the board
FUSED_CELL_6+: F1509.2, LSP1509.P$1; also elsewhere on the board
FUSED_CELL_7+: F1510.2, LSP1510.P$1; also elsewhere on the board
FUSED_CELL_8+: F1511.2, LSP1511.P$1; also elsewhere on the board
FUSED_CELL_9+: F1512.2, LSP1512.P$1; also elsewhere on the board
FUSED_CELL_10+: F1513.2, LSP1513.P$1; also elsewhere on the board
FUSED_CELL_11+: F1514.2, LSP1514.P$1; also elsewhere on the board
FUSED_VBAT+: F1515.2, LSP1515.P$1; also elsewhere on the board
FUSED_VBAT-: F1501.2, LSP1501.P$1; also elsewhere on the board
VBAT+: F1515.1, SJ1502.1; also elsewhere on the board
VBAT-: F1501.1, SJ1501.2; also elsewhere on the board
